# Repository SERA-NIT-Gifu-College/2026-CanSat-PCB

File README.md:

# 2026-CanSat-PCB
PCB for CanSat 2026

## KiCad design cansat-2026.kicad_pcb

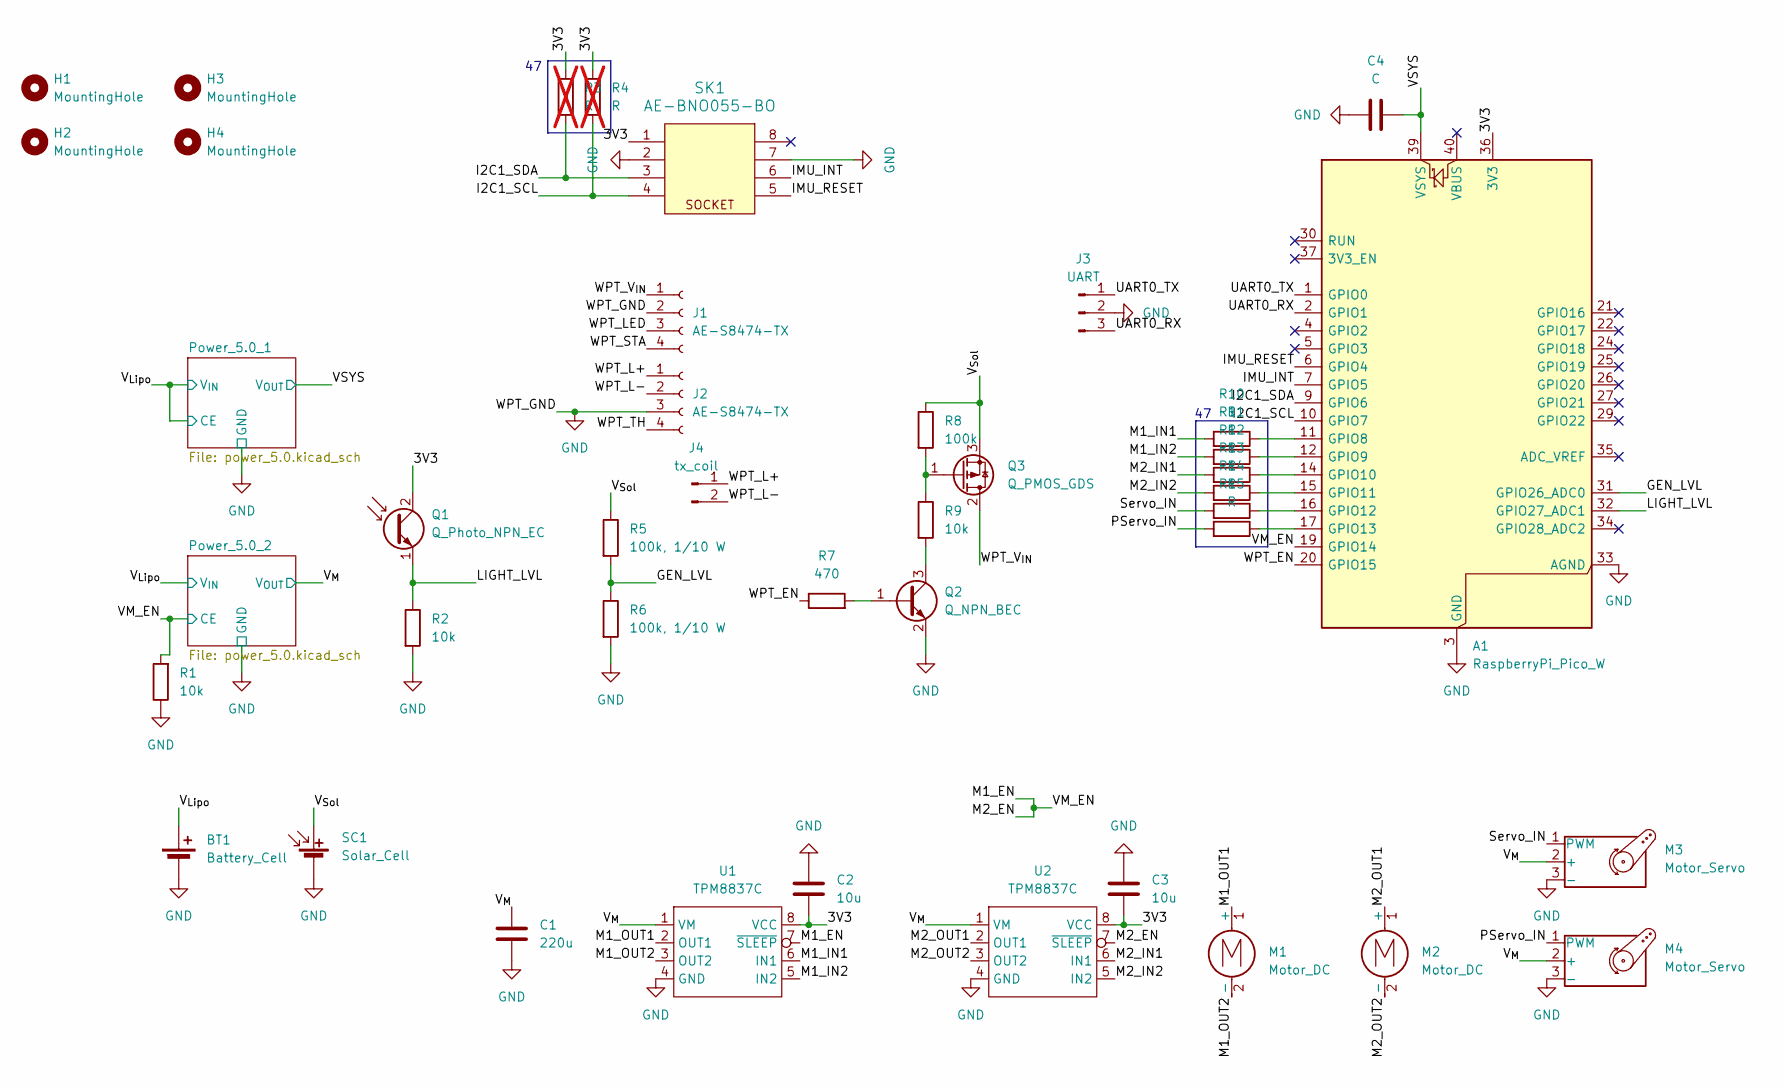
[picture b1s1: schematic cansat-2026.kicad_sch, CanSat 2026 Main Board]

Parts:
A1: RaspberryPi_Pico_W; RaspberryPi_Pico_Common_THT
BT1: Battery_Cell; JST_PH_B2B-PH-K_1x02_P2.00mm_Vertical
C1: 220u; C_Radial_D8.0mm_H7.0mm_P3.50mm
C2, C3: 10u; C_0603_1608Metric
C4: C; C_0603_1608Metric
H1, H2, H3, H4: MountingHole; MountingHole_3.2mm_M3
J1, J2: AE-S8474-TX; PinSocket_1x04_P2.54mm_Vertical
J3: UART; PinHeader_1x03_P2.54mm_Vertical
J4: tx_coil; PinSocket_1x02_P2.54mm_Vertical
M1, M2: Motor_DC; PinHeader_1x02_P2.54mm_Vertical
M3, M4: Motor_Servo; PinHeader_1x03_P2.54mm_Vertical
Q1: Q_Photo_NPN_EC; LED_D3.0mm
Q2: Q_NPN_BEC; SOT-23-3
Q3: Q_PMOS_GDS; TO-252-2
R1, R2, R9: 10k; R_0603_1608Metric
R3, R4: R; R_0603_1608Metric; not fitted
R5, R6: 100k, 1/10 W; R_0603_1608Metric
R7: 470; R_0603_1608Metric
R8: 100k; R_0603_1608Metric
R10, R11, R12, R13, R14, R15: R; R_0603_1608Metric
SC1: Solar_Cell; JST_PH_B2B-PH-K_1x02_P2.00mm_Vertical
SK1: AE-BNO055-BO; DIP-8_W7.62mm
U1, U2: TPM8837C; SOP-8_3.76x4.96mm_P1.27mm

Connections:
/3V3: A1.36 (3V3), C2.1, C3.1, Q1.2 (C), R3.1, R4.1, SK1.1, U1.8 (VCC), U2.8 (VCC)
/GEN_LVL: A1.31 (GPIO26_ADC0), R5.2, R6.1
/I2C1_SCL: A1.10 (GPIO7), R4.2, SK1.4
/I2C1_SDA: A1.9 (GPIO6), R3.2, SK1.3
/IMU_INT: A1.7 (GPIO5), SK1.6
/IMU_RESET: A1.6 (GPIO4), SK1.5
/LIGHT_LVL: A1.32 (GPIO27_ADC1), Q1.1 (E), R2.1
/M1_EN: A1.19 (GPIO14), R1.2, U1.7 (~SLEEP), U2.7 (~SLEEP); also elsewhere on the board
/M1_IN1: R10.2, U1.6 (IN1)
/M1_IN2: R11.2, U1.5 (IN2)
/M1_OUT1: M1.1 (+), U1.2 (OUT1)
/M1_OUT2: M1.2 (-), U1.3 (OUT2)
/M2_IN1: R12.2, U2.6 (IN1)
/M2_IN2: R13.2, U2.5 (IN2)
/M2_OUT1: M2.1 (+), U2.2 (OUT1)
/M2_OUT2: M2.2 (-), U2.3 (OUT2)
/PServo_IN: M4.1 (PWM), R15.2
/Servo_IN: M3.1 (PWM), R14.2
/UART0_RX: A1.2 (GPIO1), J3.3
/UART0_TX: A1.1 (GPIO0), J3.1
/VSYS: A1.39 (VSYS), C4.2; also elsewhere on the board
/V_{Lipo}: BT1.1 (+); also elsewhere on the board
/V_{M}: C1.1, M3.2 (+), M4.2 (+), U1.1 (VM), U2.1 (VM); also elsewhere on the board
/V_{Sol}: Q3.3 (S), R5.1, R8.1, SC1.1 (+)
/WPT_EN: A1.20 (GPIO15), R7.1
/WPT_L+: J2.1, J4.1
/WPT_L-: J2.2, J4.2
/WPT_LED: J1.3
/WPT_STA: J1.4
/WPT_TH: J2.4
/WPT_V_{IN}: J1.1, Q3.2 (D)
GND: A1.3 (GND), A1.8 (GND), A1.13 (GND), A1.18 (GND), A1.23 (GND), A1.28 (GND), A1.33 (AGND), A1.38 (GND), BT1.2 (-), C1.2, C2.2, C3.2, C4.1, J1.2, J2.3, J3.2, M3.3 (-), M4.3 (-), Q2.2 (E), R1.1, R2.2, R6.2, SC1.2 (-), SK1.2, SK1.7, U1.4 (GND), U2.4 (GND); also elsewhere on the board
unnamed: A1.11 (GPIO8), R10.1
unnamed: A1.12 (GPIO9), R11.1
unnamed: A1.14 (GPIO10), R12.1
unnamed: A1.15 (GPIO11), R13.1
unnamed: A1.16 (GPIO12), R14.1
unnamed: A1.17 (GPIO13), R15.1
unnamed: Q2.1 (B), R7.2
unnamed: Q2.3 (C), R9.2
unnamed: Q3.1 (G), R8.2, R9.1

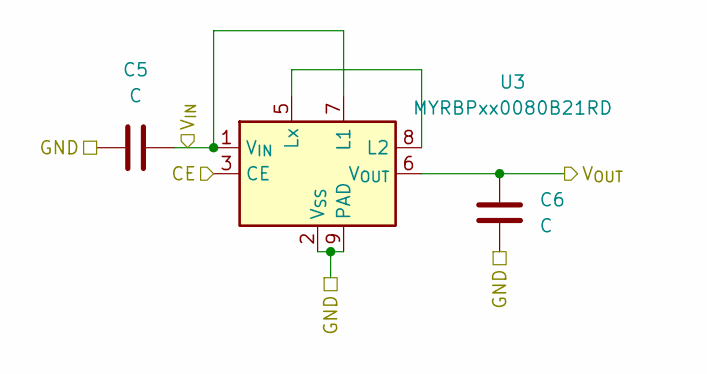
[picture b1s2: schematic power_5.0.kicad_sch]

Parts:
C5, C6: C; C_0603_1608Metric
U3: MYRBPxx0080B21RD; Converter_DCDC_Murata_MYRxP

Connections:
/VSYS: C6.1, U3.6 (V_{OUT}); also elsewhere on the board
/V_{Lipo}: C5.2, U3.1 (V_{IN}), U3.3 (CE), U3.7 (L1); also elsewhere on the board
GND: C5.1, C6.2, U3.2 (V_{SS}), U3.4 (V_{SS}), U3.9 (PAD); also elsewhere on the board
unnamed: U3.5 (Lx), U3.8 (L2)

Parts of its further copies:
C7, C8: C; C_0603_1608Metric
U4: MYRBPxx0080B21RD; Converter_DCDC_Murata_MYRxP

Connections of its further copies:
/M1_EN: U4.3 (CE); also elsewhere on the board
/V_{Lipo}: C7.2, U4.1 (V_{IN}), U4.7 (L1); also elsewhere on the board
/V_{M}: C8.1, U4.6 (V_{OUT}); also elsewhere on the board
GND: C7.1, C8.2, U4.2 (V_{SS}), U4.4 (V_{SS}), U4.9 (PAD); also elsewhere on the board
unnamed: U4.5 (Lx), U4.8 (L2)

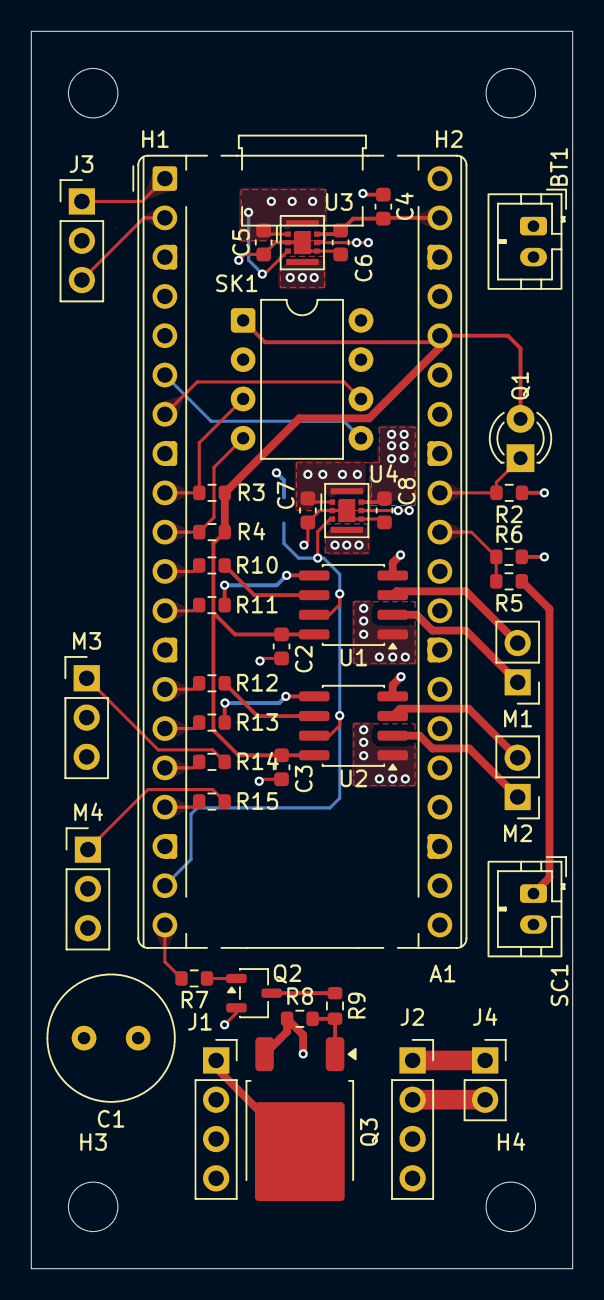
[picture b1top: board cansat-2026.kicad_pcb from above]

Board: 4 copper layers, 35.0 x 80.0 mm, 46 parts (1 on the bottom side), 40 nets.
